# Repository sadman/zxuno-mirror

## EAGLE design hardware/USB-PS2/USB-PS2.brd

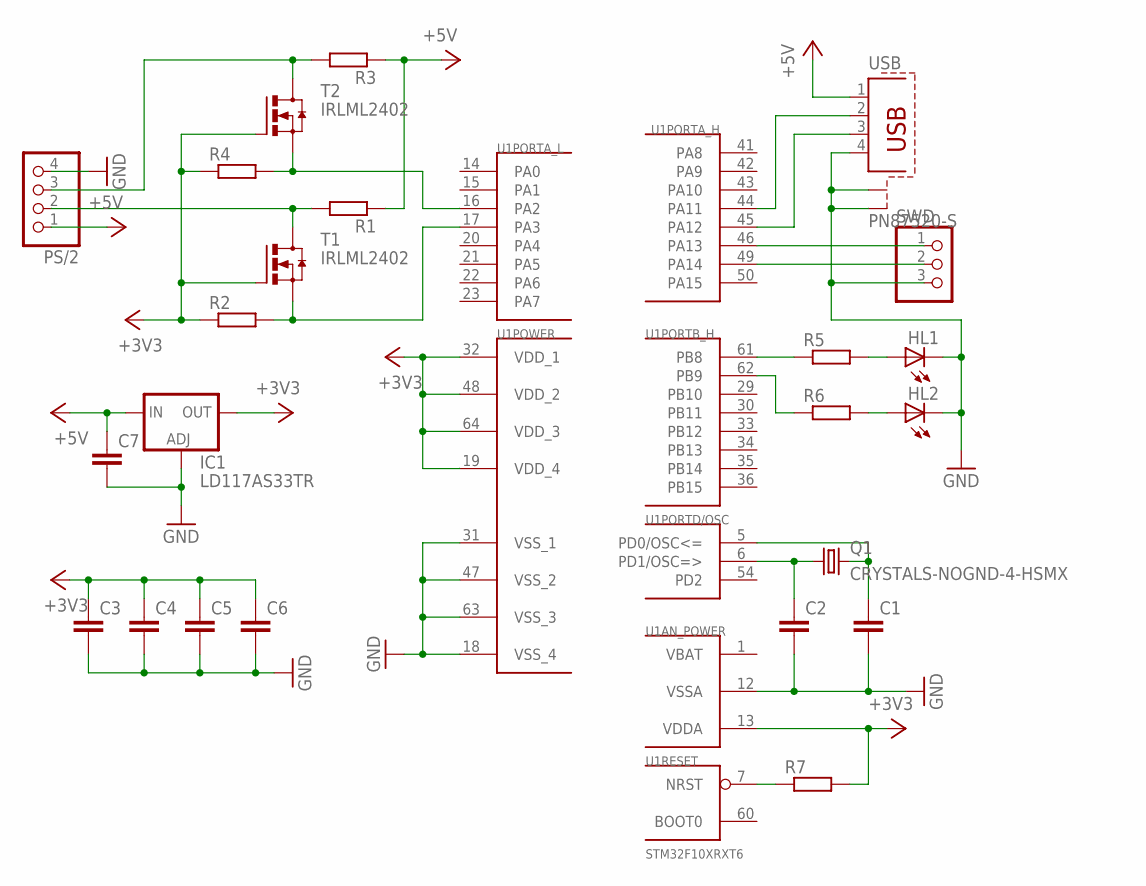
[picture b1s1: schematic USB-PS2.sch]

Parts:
C1, C2, C3, C4, C5, C6, C7: C-EUC0603K; C0603K
HL1, HL2: LEDSML0805; SML0805
IC1: LD117AS33TR; SOT223
PS/2: PINHD-1X4; 1X04
Q1: CRYSTALS-NOGND-4-HSMX; HC49-4-HSMX
R1, R2, R3, R4, R5, R6, R7: R-EU_R0603; R0603
SWD: PINHD-1X3; 1X03
T1, T2: IRLML2402; MICRO3
U1: STM32F10XRXT6; TQFP64
USB: PN87520-S

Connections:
+3V3: C3.1, C4.1, C5.1, C6.1, IC1.4 (OUT), R2.1, R4.1, R7.2, T1.1 (G), T2.1 (G), U1.13 (VDDA), U1.19 (VDD_4), U1.32 (VDD_1), U1.48 (VDD_2), U1.64 (VDD_3)
+5V: C7.1, IC1.3 (IN), PS/2.1, R1.1, R3.1, USB.1
GND: C1.2, C2.2, C3.2, C4.2, C5.2, C6.2, C7.2, HL1.C, HL2.C, IC1.1 (ADJ), PS/2.4, SWD.3, U1.12 (VSSA), U1.18 (VSS_4), U1.31 (VSS_1), U1.47 (VSS_2), U1.63 (VSS_3), USB.4, USB.S1, USB.S2
unnamed: U1.44 (PA11), USB.2
unnamed: U1.45 (PA12), USB.3
unnamed: R5.1, U1.61 (PB8)
unnamed: C1.1, Q1.2, U1.5 (PD0/OSC<=)
unnamed: HL1.A, R5.2
unnamed: HL2.A, R6.2
unnamed: R6.1, U1.62 (PB9)
unnamed: C2.1, Q1.1, U1.6 (PD1/OSC=>)
unnamed: R7.1, U1.7 (NRST)
unnamed: R2.2, T1.2 (S), U1.17 (PA3)
unnamed: R4.2, T2.2 (S), U1.16 (PA2)
PS2_CLK: PS/2.2, R1.2, T1.3 (D)
PS2_DAT: PS/2.3, R3.2, T2.3 (D)
SWCLK: SWD.2, U1.49 (PA14)
SWDIO: SWD.1, U1.46 (PA13)
VBAT: U1.1 (VBAT)

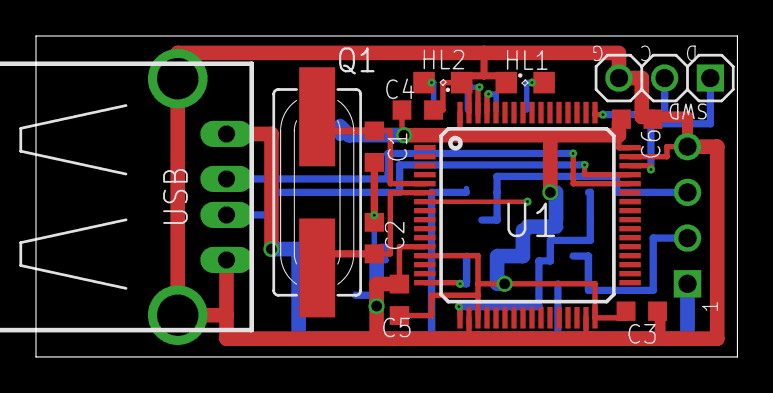
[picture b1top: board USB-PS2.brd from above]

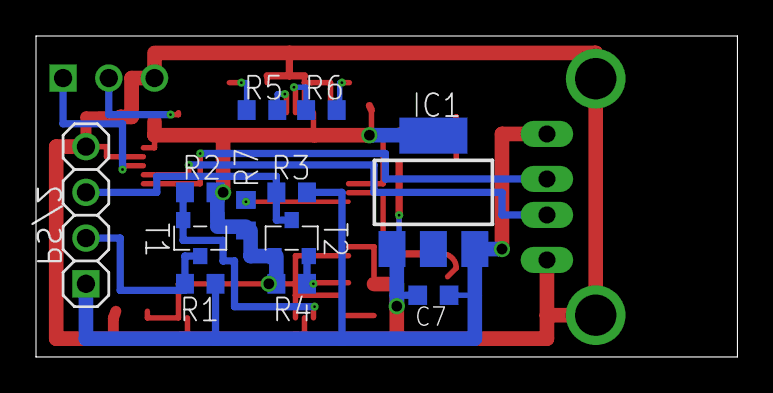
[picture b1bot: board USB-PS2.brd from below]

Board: 2 copper layers, 39.0 x 17.8 mm, 24 parts (12 on the bottom side), 18 nets.

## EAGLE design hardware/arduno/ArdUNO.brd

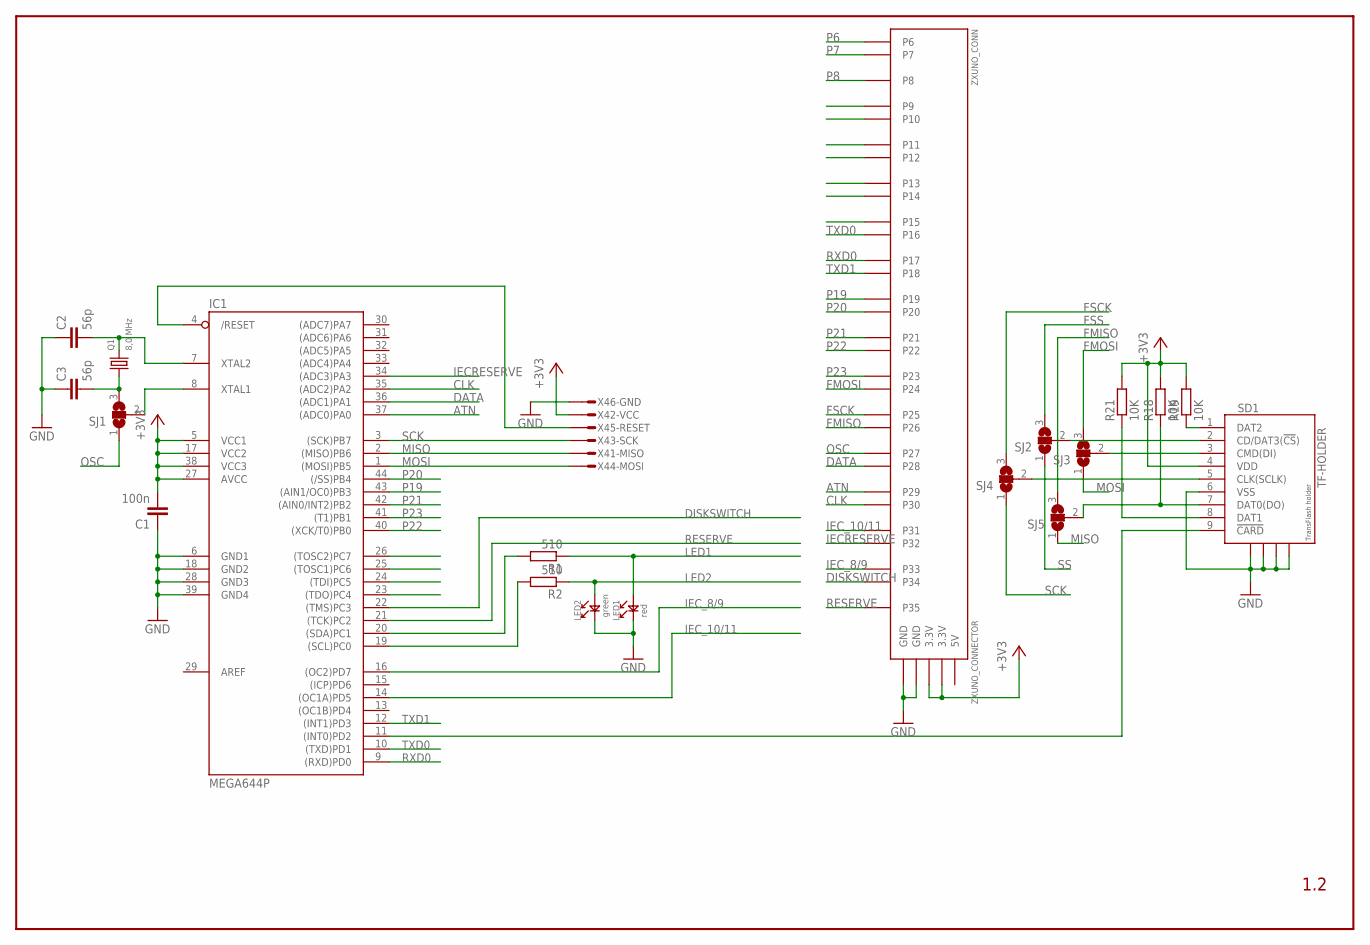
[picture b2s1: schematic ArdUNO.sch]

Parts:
C1: 100n; C0805
C2, C3: 56p; C0805
IC1: MEGA644P; TQFP44
LED1: red; LED0805
LED2: green; LED0805
Q1: 8,0 MHz; HC49/S
R1, R2: 510; R0805
R18, R19, R21: 10K; R0805
SD1: TF-HOLDER; TF-PULL
SJ1, SJ2, SJ3, SJ4, SJ5: SJ2W; SJ_2
X4: AVR-ISP_1X6; 1X6_ISP
ZXUNO_CONN: ZXUNO_CONNECTOR

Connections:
5V: ZXUNO_CONN.5V
+3V3: C1.2, IC1.5 (VCC1), IC1.17 (VCC2), IC1.27 (AVCC), IC1.38 (VCC3), R18.2, R19.2, R21.2, SD1.4 (VDD), X4.2, ZXUNO_CONN.3.3V@1 (3.3V), ZXUNO_CONN.3.3V@2 (3.3V)
/RESET: IC1.4 (/RESET), X4.5
ATN: IC1.37 ((ADC0)PA0), ZXUNO_CONN.P29
CD: IC1.11 ((INT0)PD2), SD1.9 (!CARD)
CLK: IC1.35 ((ADC2)PA2), ZXUNO_CONN.P30
DATA: IC1.36 ((ADC1)PA1), ZXUNO_CONN.P28
DISKSWITCH: IC1.22 ((TMS)PC3), ZXUNO_CONN.P34
FMISO: SJ5.3, ZXUNO_CONN.P26
FMOSI: SJ3.3, ZXUNO_CONN.P24
FSCK: SJ4.3, ZXUNO_CONN.P25
FSS: SJ2.3
GND: C1.1, C2.1, C3.1, IC1.6 (GND1), IC1.18 (GND2), IC1.28 (GND3), IC1.39 (GND4), LED1.1, LED2.1, SD1.6 (VSS), SD1.S1, SD1.S2, SD1.S3, SD1.S4, X4.6, ZXUNO_CONN.GND@1 (GND), ZXUNO_CONN.GND@2 (GND)
IECRESERVE: IC1.34 ((ADC3)PA3), ZXUNO_CONN.P32
IEC_8/9: IC1.16 ((OC2)PD7), ZXUNO_CONN.P33
IEC_10/11: IC1.14 ((OC1A)PD5), ZXUNO_CONN.P31
LED1: LED1.2, R1.1
LED2: LED2.2, R2.1
MISO: IC1.2 ((MISO)PB6), SJ5.1, X4.1
MOSI: IC1.1 ((MOSI)PB5), SJ3.1, X4.4
unnamed: R18.1, SD1.7 (DAT0(DO)), SJ5.2
unnamed: SD1.3 (CMD(DI)), SJ3.2
unnamed: C3.2, Q1.1, SJ1.3
unnamed: C2.2, IC1.7 (XTAL2), Q1.2
unnamed: SD1.2 (CD/DAT3(!CS!)), SJ2.2
unnamed: IC1.8 (XTAL1), SJ1.2
unnamed: R19.1, SD1.1 (DAT2)
unnamed: SD1.5 (CLK(SCLK)), SJ4.2
unnamed: R21.1, SD1.8 (DAT1)
OSC: SJ1.1, ZXUNO_CONN.P27
P6: ZXUNO_CONN.P6
P7: ZXUNO_CONN.P7
P8: ZXUNO_CONN.P8
P9: ZXUNO_CONN.P9
P10: ZXUNO_CONN.P10
P11: ZXUNO_CONN.P11
P12: ZXUNO_CONN.P12
P13: ZXUNO_CONN.P13
P14: ZXUNO_CONN.P14
P15: ZXUNO_CONN.P15
P19: IC1.43 ((AIN1/OC0)PB3), ZXUNO_CONN.P19
P20: IC1.44 ((/SS)PB4), ZXUNO_CONN.P20
P21: IC1.42 ((AIN0/INT2)PB2), ZXUNO_CONN.P21
P22: IC1.40 ((XCK/T0)PB0), ZXUNO_CONN.P22
P23: IC1.41 ((T1)PB1), ZXUNO_CONN.P23
PC0: IC1.19 ((SCL)PC0), R2.2
PC1: IC1.20 ((SDA)PC1), R1.2
RESERVE: IC1.21 ((TCK)PC2), ZXUNO_CONN.P35
RXD0: IC1.9 ((RXD)PD0), ZXUNO_CONN.P17
SCK: IC1.3 ((SCK)PB7), SJ4.1, X4.3
SS: SJ2.1
TXD0: IC1.10 ((TXD)PD1), ZXUNO_CONN.P16
TXD1: IC1.12 ((INT1)PD3), ZXUNO_CONN.P18

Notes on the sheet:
1.2

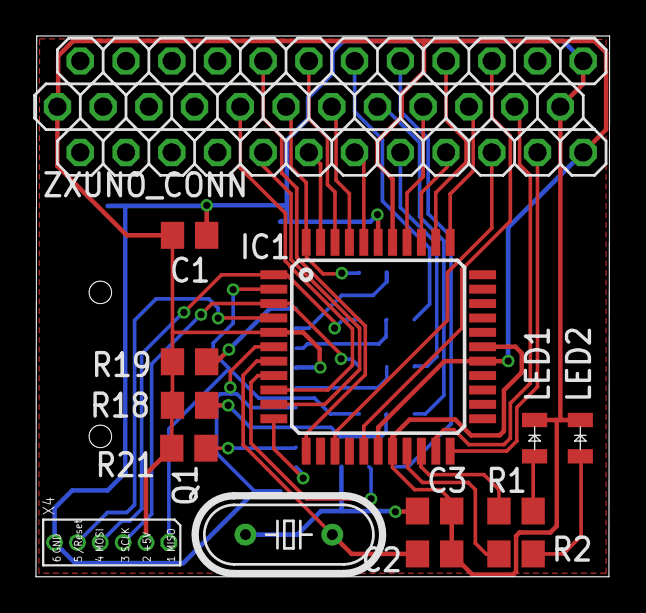
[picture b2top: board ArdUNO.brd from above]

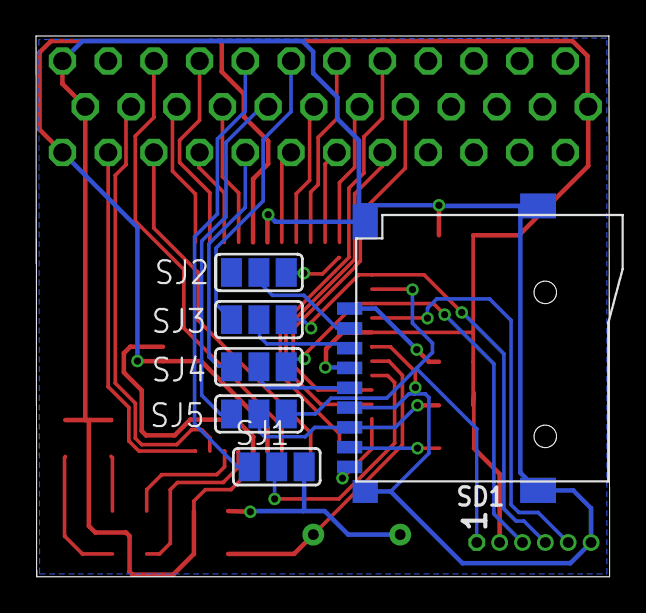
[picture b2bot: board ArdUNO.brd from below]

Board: 2 copper layers, 31.9 x 30.0 mm, 20 parts (6 on the bottom side), 40 nets.

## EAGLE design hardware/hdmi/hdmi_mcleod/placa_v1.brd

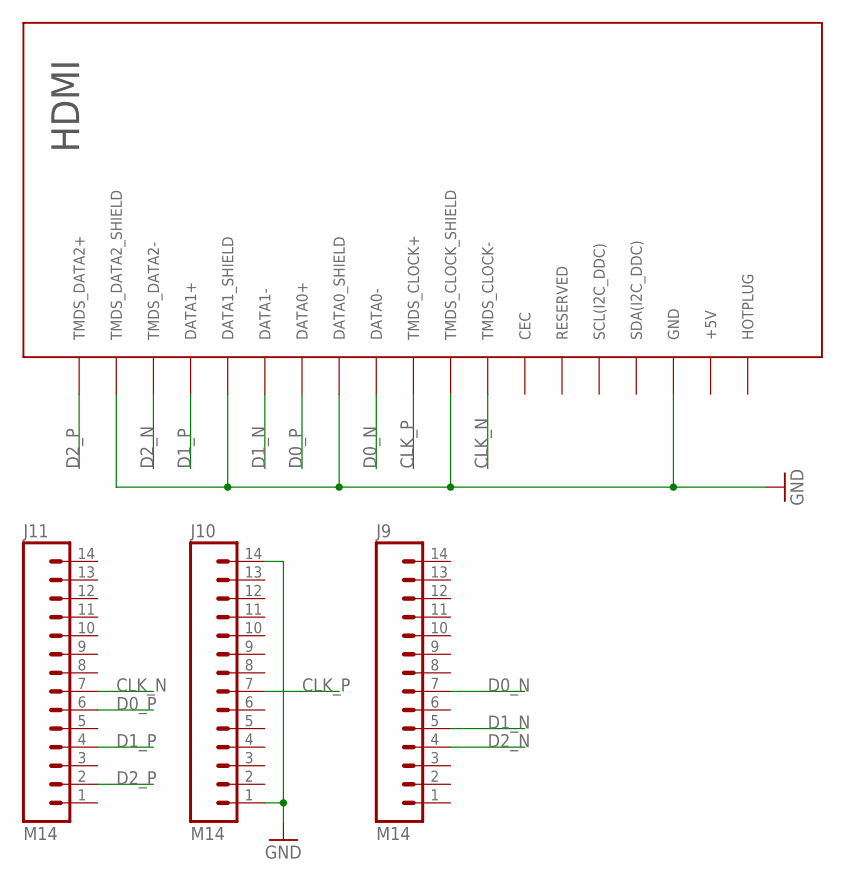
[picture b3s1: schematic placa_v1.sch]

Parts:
J9, J10, J11: M14; 1X14
U$1: HDMI

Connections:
CLK_N: J11.7, U$1.P$8 (TMDS_CLOCK-)
CLK_P: J10.7, U$1.P$10 (TMDS_CLOCK+)
D0_N: J9.7, U$1.P$11 (DATA0-)
D0_P: J11.6, U$1.P$13 (DATA0+)
D1_N: J9.5, U$1.P$14 (DATA1-)
D1_P: J11.4, U$1.P$16 (DATA1+)
D2_N: J9.4, U$1.P$17 (TMDS_DATA2-)
D2_P: J11.2, U$1.P$19 (TMDS_DATA2+)
GND: J10.1, J10.14, U$1.P$3 (GND), U$1.P$9 (TMDS_CLOCK_SHIELD), U$1.P$12 (DATA0_SHIELD), U$1.P$15 (DATA1_SHIELD), U$1.P$18 (TMDS_DATA2_SHIELD)

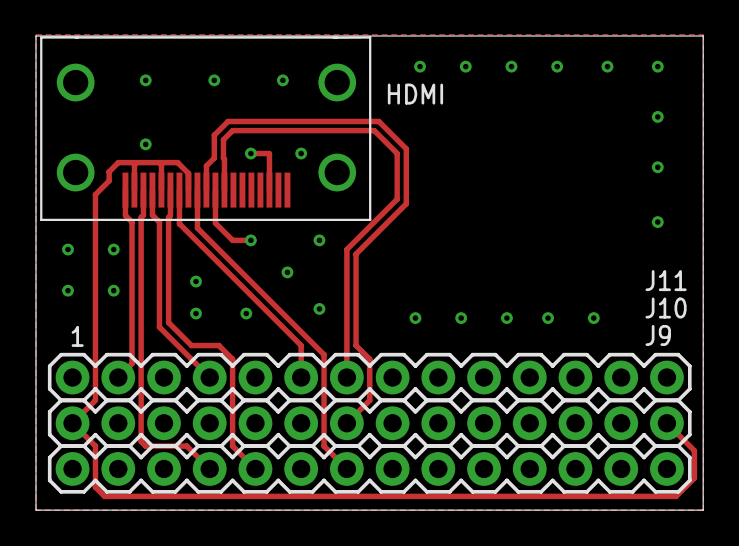
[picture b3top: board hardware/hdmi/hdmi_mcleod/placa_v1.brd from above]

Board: 2 copper layers, 37.1 x 26.3 mm, 4 parts (0 on the bottom side), 9 nets.

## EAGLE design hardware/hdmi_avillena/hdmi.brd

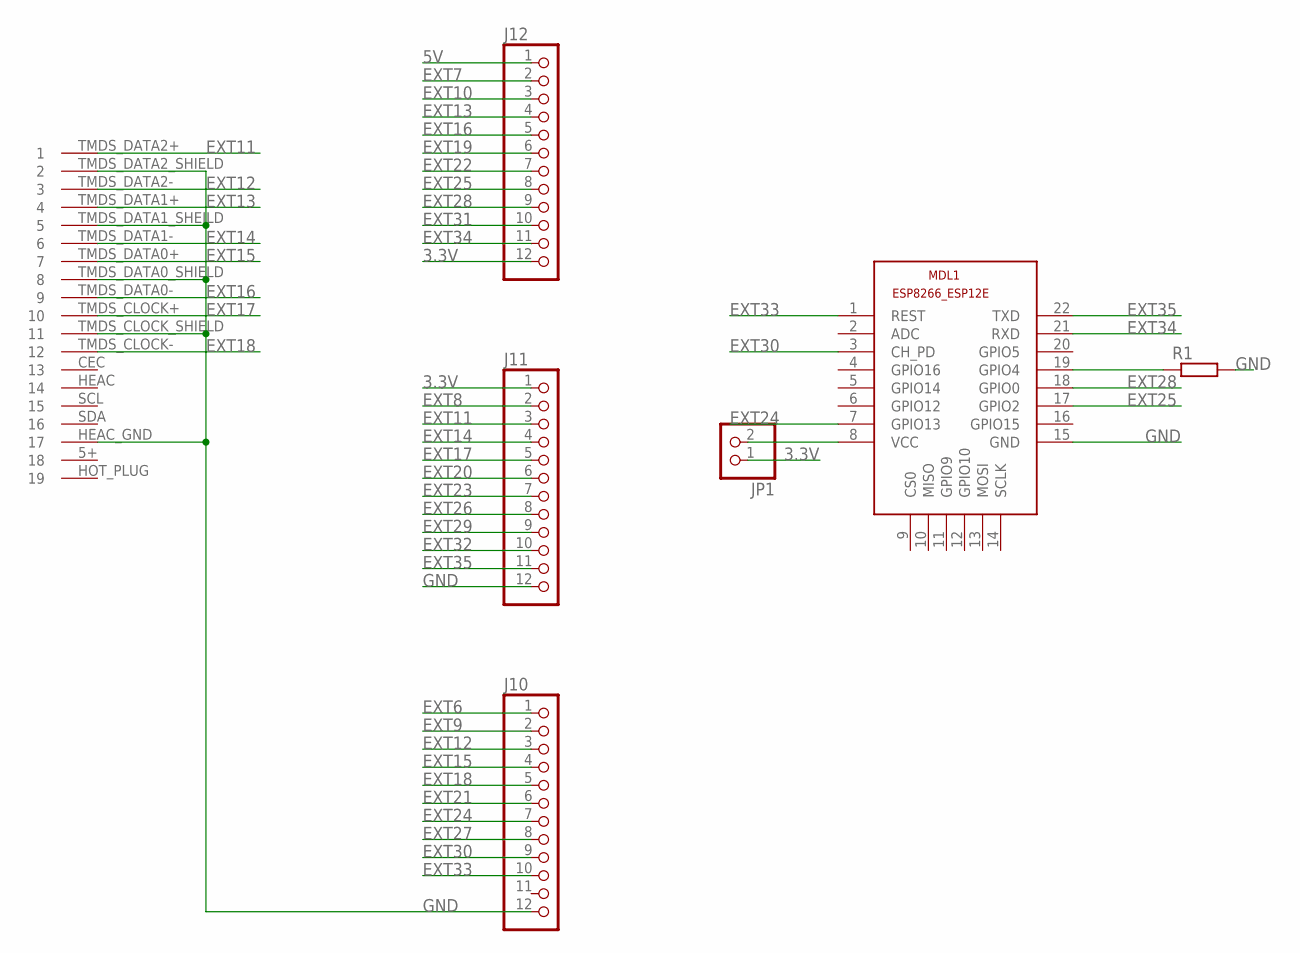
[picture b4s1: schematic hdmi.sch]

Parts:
J10, J11, J12: PINHD-1X12; 1X12
JP1: PINHD-1X2/90; 1X02/90
MDL1: ESP8266-12EESP8266-ESP12E; ESP8266-ESP12E
R1: R-EU_M0805; M0805
U$2: HDMI; DS1115

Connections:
3.3V: J11.1, J12.12, JP1.1
5V: J12.1
EXT6: J10.1
EXT7: J12.2
EXT8: J11.2
EXT9: J10.2
EXT10: J12.3
EXT11: J11.3, U$2.TMDS_DATA2+ (1)
EXT12: J10.3, U$2.TMDS_DATA2- (3)
EXT13: J12.4, U$2.TMDS_DATA1+ (4)
EXT14: J11.4, U$2.TMDS_DATA1- (6)
EXT15: J10.4, U$2.TMDS_DATA0+ (7)
EXT16: J12.5, U$2.TMDS_DATA0- (9)
EXT17: J11.5, U$2.TMDS_CLOCK+ (10)
EXT18: J10.5, U$2.TMDS_CLOCK- (12)
EXT19: J12.6
EXT20: J11.6
EXT21: J10.6
EXT22: J12.7
EXT23: J11.7
EXT24: J10.7, MDL1.7 (GPIO13)
EXT25: J12.8, MDL1.17 (GPIO2)
EXT26: J11.8
EXT27: J10.8
EXT28: J12.9, MDL1.18 (GPIO0)
EXT29: J11.9
EXT30: J10.9, MDL1.3 (CH_PD)
EXT31: J12.10
EXT32: J11.10
EXT33: J10.10, MDL1.1 (REST)
EXT34: J12.11, MDL1.21 (RXD)
EXT35: J11.11, MDL1.22 (TXD)
GND: J10.12, J11.12, MDL1.15 (GND), R1.2, U$2.HEAC_GND (17), U$2.TMDS_CLOCK_SHIELD (11), U$2.TMDS_DATA0_SHIELD (8), U$2.TMDS_DATA1_SHEILD (5), U$2.TMDS_DATA2_SHIELD (2)
unnamed: MDL1.19 (GPIO4), R1.1
unnamed: JP1.2, MDL1.8 (VCC)

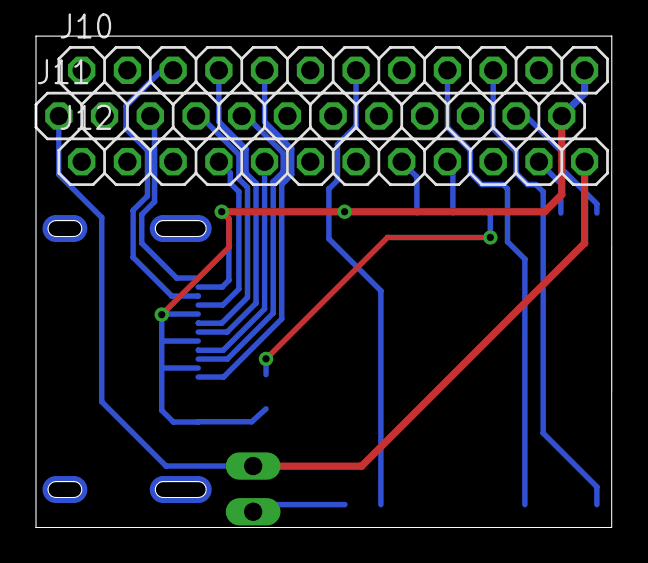
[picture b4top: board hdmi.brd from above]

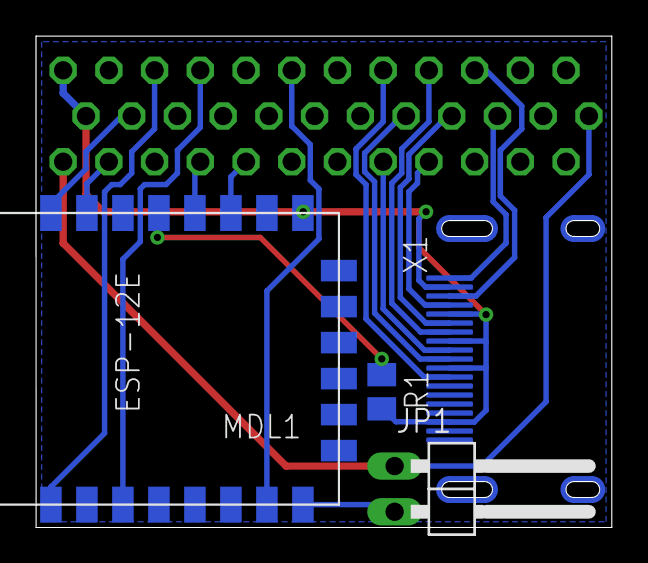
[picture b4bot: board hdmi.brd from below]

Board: 2 copper layers, 32.0 x 27.3 mm, 7 parts (4 on the bottom side), 19 nets.

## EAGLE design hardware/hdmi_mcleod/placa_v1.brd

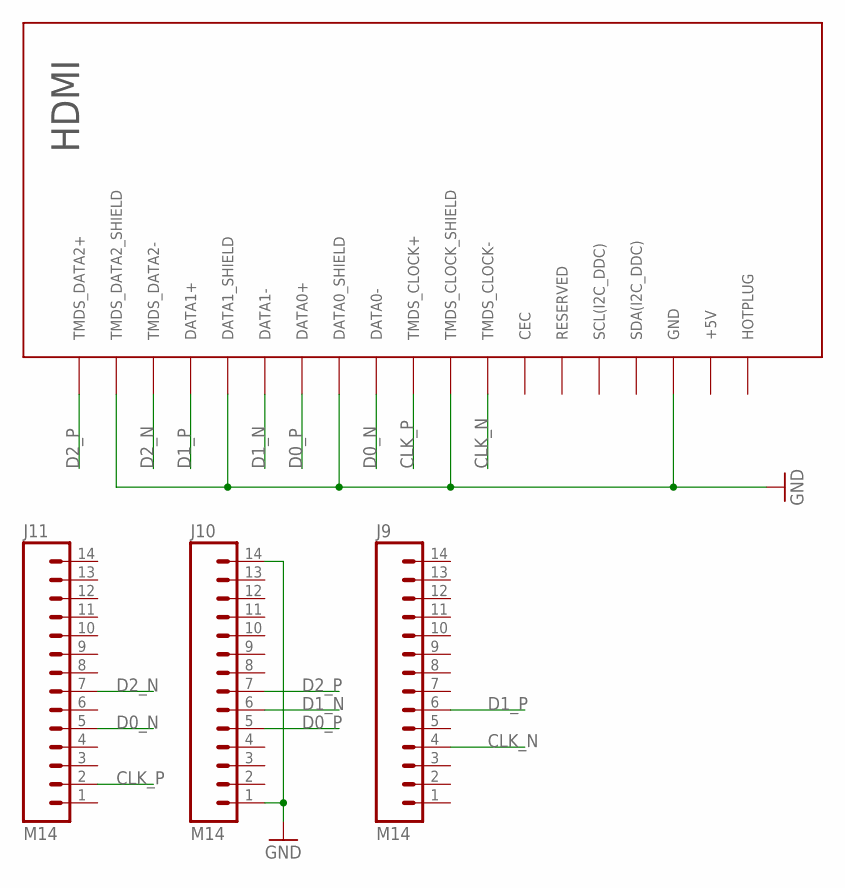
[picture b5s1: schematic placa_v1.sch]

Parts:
J9, J10, J11: M14; 1X14
U$1: HDMI

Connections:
CLK_N: J9.4, U$1.P$8 (TMDS_CLOCK-)
CLK_P: J11.2, U$1.P$10 (TMDS_CLOCK+)
D0_N: J11.5, U$1.P$11 (DATA0-)
D0_P: J10.5, U$1.P$13 (DATA0+)
D1_N: J10.6, U$1.P$14 (DATA1-)
D1_P: J9.6, U$1.P$16 (DATA1+)
D2_N: J11.7, U$1.P$17 (TMDS_DATA2-)
D2_P: J10.7, U$1.P$19 (TMDS_DATA2+)
GND: J10.1, J10.14, U$1.P$3 (GND), U$1.P$9 (TMDS_CLOCK_SHIELD), U$1.P$12 (DATA0_SHIELD), U$1.P$15 (DATA1_SHIELD), U$1.P$18 (TMDS_DATA2_SHIELD)

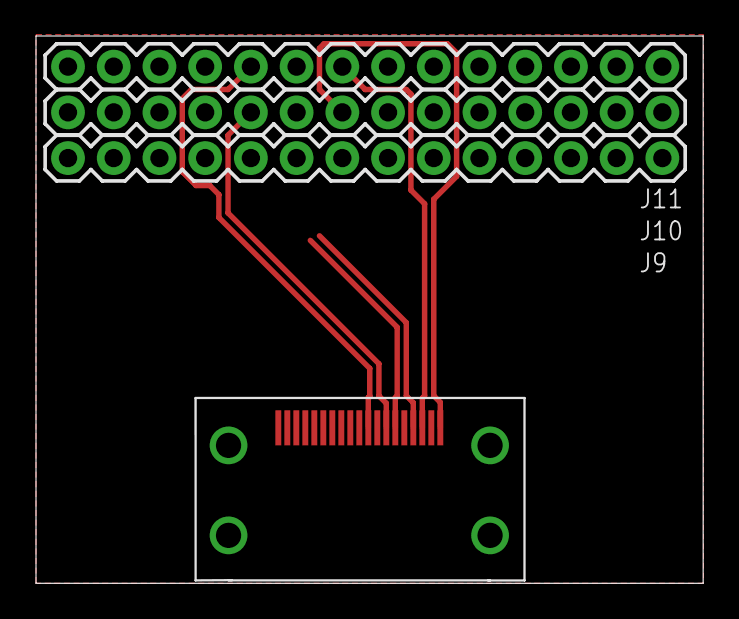
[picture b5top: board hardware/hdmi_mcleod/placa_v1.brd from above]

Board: 2 copper layers, 37.1 x 30.4 mm, 4 parts (0 on the bottom side), 9 nets.

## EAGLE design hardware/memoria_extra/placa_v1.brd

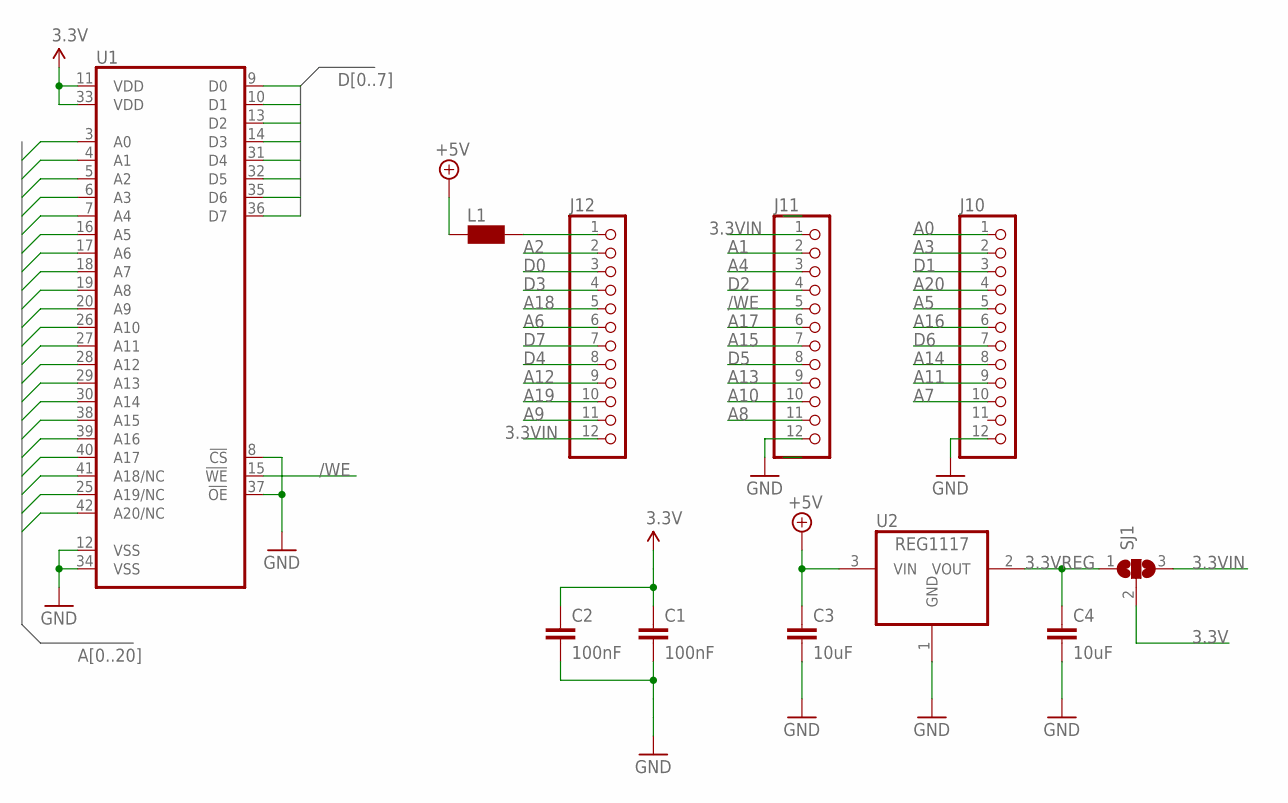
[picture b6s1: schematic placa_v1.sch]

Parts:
C1, C2: 100nF; C0805K
C3, C4: 10uF; C0805K
J10, J11, J12: PINHD-1X12; 1X12
L1: WE-CBF_0805; 0805
SJ1: SJ2W; SJ_2
U1: ISSI_SRAM_8BIT; TSOP44-II
U2: REG1117; SOT223

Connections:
3.3V: C1.1, C2.1, SJ1.2, U1.11 (VDD), U1.33 (VDD)
3.3VIN: J11.1, J12.12, SJ1.3
3.3VREG: C4.1, SJ1.1, U2.2 (VOUT)
+5V: C3.1, L1.2, U2.3 (VIN)
/WE: J11.5, U1.15 (!WE)
A0: J10.1, U1.3 (A0)
A1: J11.2, U1.4 (A1)
A2: J12.2, U1.5 (A2)
A3: J10.2, U1.6 (A3)
A4: J11.3, U1.7 (A4)
A5: J10.5, U1.16 (A5)
A6: J12.6, U1.17 (A6)
A7: J10.10, U1.18 (A7)
A8: J11.11, U1.19 (A8)
A9: J12.11, U1.20 (A9)
A10: J11.10, U1.26 (A10)
A11: J10.9, U1.27 (A11)
A12: J12.9, U1.28 (A12)
A13: J11.9, U1.29 (A13)
A14: J10.8, U1.30 (A14)
A15: J11.7, U1.38 (A15)
A16: J10.6, U1.39 (A16)
A17: J11.6, U1.40 (A17)
A18: J12.5, U1.41 (A18/NC)
A19: J12.10, U1.25 (A19/NC)
A20: J10.4, U1.42 (A20/NC)
D0: J12.3, U1.9 (D0)
D1: J10.3, U1.10 (D1)
D2: J11.4, U1.13 (D2)
D3: J12.4, U1.14 (D3)
D4: J12.8, U1.31 (D4)
D5: J11.8, U1.32 (D5)
D6: J10.7, U1.35 (D6)
D7: J12.7, U1.36 (D7)
GND: C1.2, C2.2, C3.2, C4.2, J10.12, J11.12, U1.8 (!CS), U1.12 (VSS), U1.34 (VSS), U1.37 (!OE), U2.1 (GND)
unnamed: J12.1, L1.1

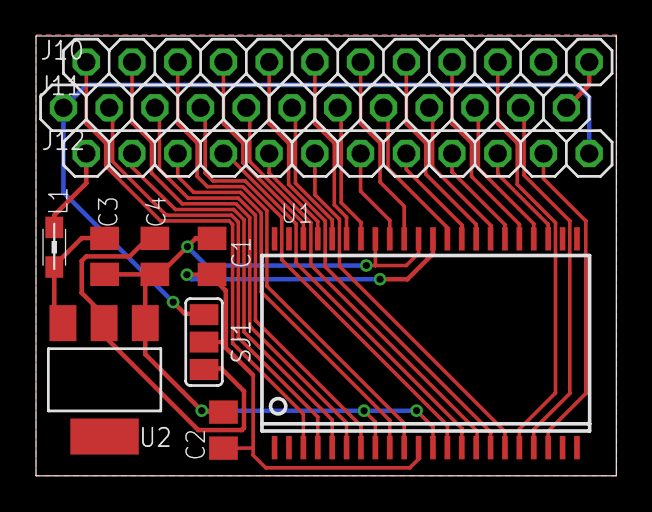
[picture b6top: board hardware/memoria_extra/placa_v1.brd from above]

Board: 2 copper layers, 32.2 x 24.4 mm, 11 parts (0 on the bottom side), 36 nets.

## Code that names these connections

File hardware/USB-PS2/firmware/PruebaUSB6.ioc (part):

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Mcu.Name=STM32F105R(8-B-C)Tx
Mcu.Package=LQFP64
Mcu.UserName=STM32F105RBTx
PA11.Mode=Host_Only
PA11.Signal=USB_OTG_FS_DM
PA12.Mode=Host_Only
PA12.Signal=USB_OTG_FS_DP
PA13.Mode=Trace_Asynchronous_SW
PA13.Signal=SYS_JTMS-SWDIO
PA14.Mode=Trace_Asynchronous_SW
PA14.Signal=SYS_JTCK-SWCLK
PA2.GPIOParameters=GPIO_Speed,PinState,GPIO_Label
PA2.GPIO_Label=PS2_DATA_PIN
PA2.GPIO_Speed=GPIO_SPEED_FREQ_HIGH
PA2.PinState=GPIO_PIN_RESET
PA2.Signal=GPIO_Output
PA3.GPIOParameters=GPIO_Speed,PinState,GPIO_Label
PA3.GPIO_Label=PS2_CLK_PIN
PA3.GPIO_Speed=GPIO_SPEED_FREQ_HIGH
PA3.PinState=GPIO_PIN_RESET
PA3.Signal=GPIO_Output
PB10.Mode=Asynchronous
PB10.Signal=USART3_TX
PB11.Mode=Asynchronous
PB11.Signal=USART3_RX
PB3.Mode=Trace_Asynchronous_SW
PB3.Signal=SYS_TRACESWO
PD0-OSC_IN.Mode=HSE-External-Oscillator
PD0-OSC_IN.Signal=RCC_OSC_IN
PD1-OSC_OUT.Mode=HSE-External-Oscillator
PD1-OSC_OUT.Signal=RCC_OSC_OUT
RCC.HSE_VALUE=12000000
RCC.SYSCLKFreq_VALUE=72000000
RCC.SYSCLKSource=RCC_SYSCLKSOURCE_PLLCLK
board=PruebaUSB6

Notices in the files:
hardware/memoria_extra/placa_v1.brd:
(C)2015 mcleod_ideafix
